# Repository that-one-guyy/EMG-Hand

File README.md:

# EMG-Hand
This contains the files creating and controlling a self-designed hand based off of EMG data

The EMG data is acquired from the Backyard Brains EMG claw

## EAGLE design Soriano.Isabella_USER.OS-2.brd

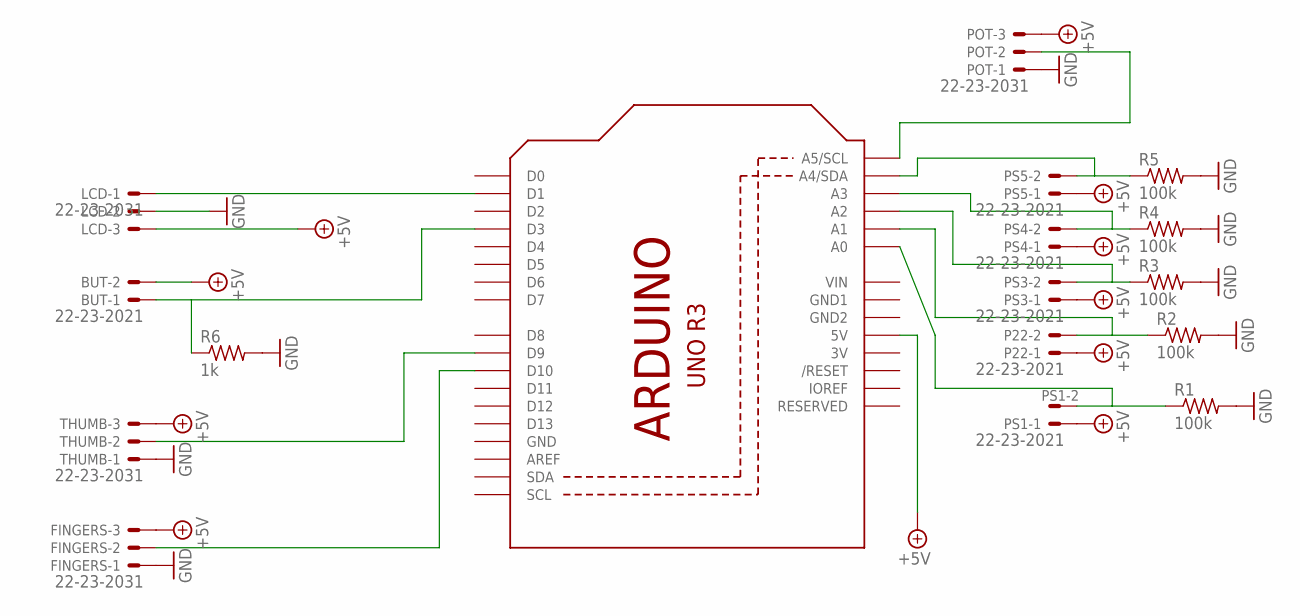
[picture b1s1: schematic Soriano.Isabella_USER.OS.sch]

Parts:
BUT: 22-23-2021
FINGERS: 22-23-2031
LCD: 22-23-2031
P22: 22-23-2021
POT: 22-23-2031
PS1, PS3, PS4, PS5: 22-23-2021
R1, R2, R3, R4, R5: 100k; R0805
R6: 1k; R0805
THUMB: 22-23-2031
U1: ARDUINOR3-BPLACE

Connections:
3V: U1.3V
+5V: BUT.2, FINGERS.3, LCD.3, P22.1, POT.3, PS1.1, PS3.1, PS4.1, PS5.1, THUMB.3, U1.5V
GND: FINGERS.1, LCD.2, POT.1, R1.2, R2.2, R3.2, R4.2, R5.2, R6.2, THUMB.1, U1.GND
GND1: U1.GND1
GND2: U1.GND2
unnamed: PS1.2, R1.1, U1.A0
unnamed: P22.2, R2.1, U1.A1
unnamed: PS3.2, R3.1, U1.A2
unnamed: PS4.2, R4.1, U1.A3
unnamed: LCD.1, U1.D1
unnamed: PS5.2, R5.1, U1.A4 (A4/SDA)
unnamed: BUT.1, R6.1, U1.D3
unnamed: POT.2, U1.A5 (A5/SCL)
unnamed: THUMB.2, U1.D9
unnamed: FINGERS.2, U1.D10
VIN: U1.VIN

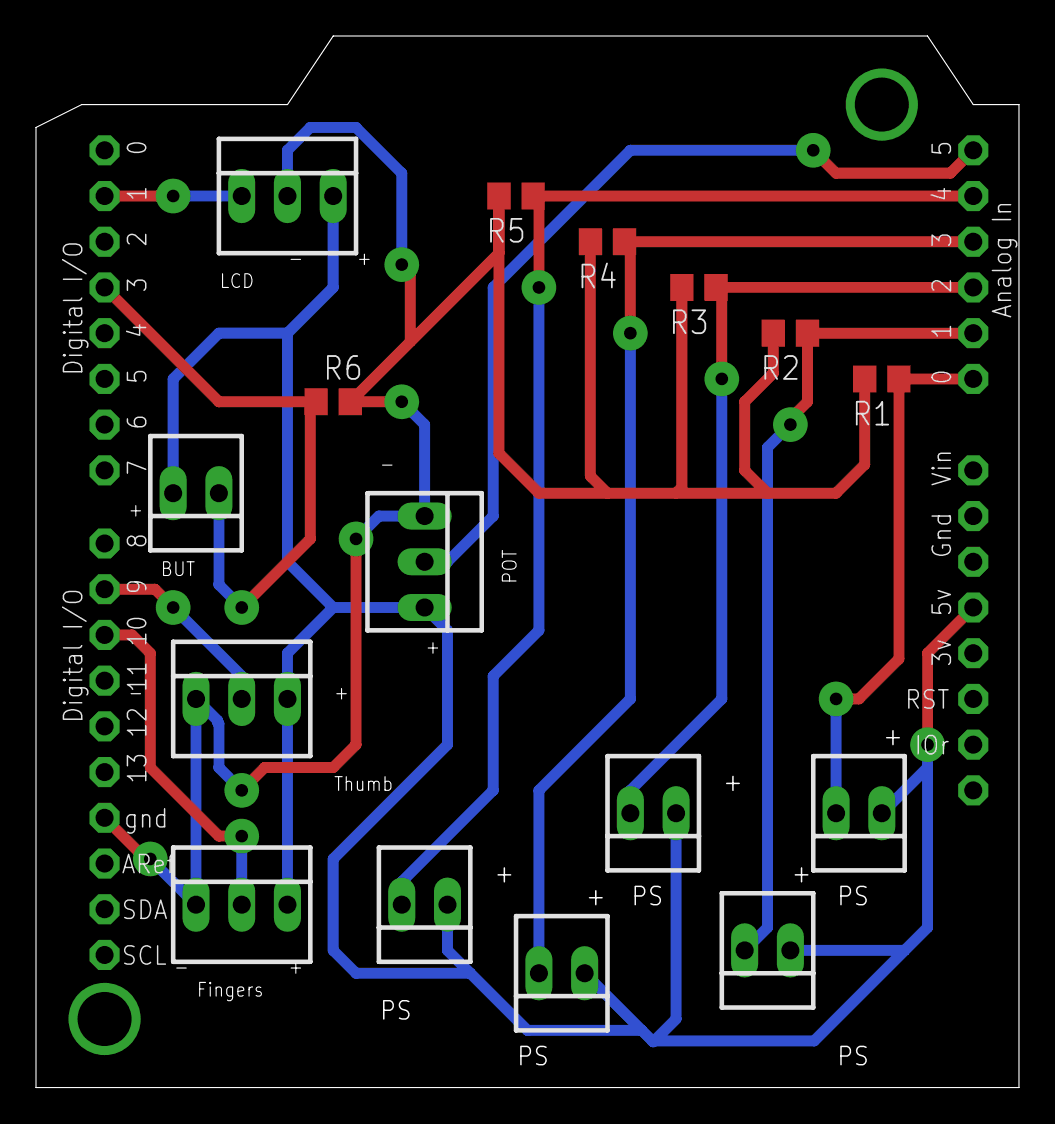
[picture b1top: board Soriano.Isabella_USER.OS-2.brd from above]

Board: 2 copper layers, 54.6 x 58.4 mm, 17 parts (0 on the bottom side), 12 nets.

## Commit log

2022-07-01 Added testing files
